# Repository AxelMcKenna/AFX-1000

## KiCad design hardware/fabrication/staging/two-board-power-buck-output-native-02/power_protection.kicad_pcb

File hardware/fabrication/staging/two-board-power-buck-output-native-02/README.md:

# Power/protection — local U23 output-capacitor bank

This checkpoint closes **eight physical connections**, bringing the power board
to **2,525 opens**. It remains **not ready for fabrication**. Open
[power_protection.kicad_pro](power_protection.kicad_pro) in KiCad.

## Placement and copper

C226–C229 retain their existing 47 µF / 25 V X7S components and footprints.
C227 moves to the front at (295,111.35) mm; C226, C228 and C229 form a back-side
bank at x=295 mm and y=111.35, 114.85 and 118.35 mm. This puts their connections
next to the inductor output, instead of beyond the regulator's feedback region.
No other component moves and no schematic pin/net assignment changes.

The front capacitor connects to L23's output with a 1 mm-wide, 5.765 mm path.
The back bank uses 1 mm-wide output and ground buses with 3.5 mm between adjacent
lands. Paired conventional 0.60/0.30 mm vias join the front and back output and
ground copper. A further pair brings the bank return to U23's PGND pin 9.
The return uses a 1 mm back-side path and a short 0.4 mm package approach.
Six vias and 17 tracks are added in 16 declared route sections.

These dimensions describe the actual construction. Effective capacitance,
loop stability, loss/temperature, switching noise and final copper-stack
capacity remain to be qualified. The output sense route and wider power/ground
planes remain unfinished. Completing this local return does not qualify the
whole power stage.

## Checks

| Item | Result |
| --- | --- |
| Electrical parts / total footprints | 1,088 / 1,103 |
| Schematic pins / mapped native pads | 3,424 / 3,485 |
| Tracks / through vias | 2,133 / 130 |
| Uncapped native opens | 2,525, down from 2,533 |
| Geometry / schematic parity / ERC errors | 0 / 0 / 0 |
| Retained isolated-reference warnings | 2 |
| Prior physical connection groups retained | All 3,271 |
| Moved footprints / changed native pads | 4 / 8 |
| Minimum drill-edge-to-SMD clearance, all vias | 0.165 mm |

The [independent audit](buck-output-audit.json) checks the saved native pad
polygons, every added track/via, the full unchanged schematic pin/net map,
unchanged earlier copper and all previous connection groups. It confirms all
four output capacitor pins connect to L23 and all four return pins connect to
U23 PGND. The eight moved pad polygons match the declared transforms within
0.000001 mm. Courtyard, board edge, mount and provisional receiving/context
checks pass; complete installed fit remains open.

The first native trial reported a copper-sliver warning. The selected successor
replaces acute and overlapping joins with shared trunks and has zero geometry
findings, with no rules suppressed. The [construction record](buck-output-routing.json)
and [native review](review.json) identify the selected source.
The [full native capture](../two-board-power-routing-inputs-2525-buck-output/capture.json)
contains 5,990 objects; its independent cluster-gap sum agrees with 2,525 opens.
The DRC output list remains capped at 499 records and is not the full open count.

## Actual copper views

| Front | Back, in top-view coordinates |
| --- | --- |
|  |  |

[Inner layers](plots/inner-contact-sheet.png) · [Local front detail](plots/local-front.png)
· [Local back detail](plots/local-back.png) · [Visual review](plots/visual-review.json)

## Remaining work

Route the output sense, configuration and enables, and complete input/ground
planes. Regroup U20/AUX and other critical circuits; route the relocated buffer's
bypass. The [source-net reconciliation](rejected-source-net-status.json) retains
eight complete and 44 incomplete formerly rejected nets. Signal main remains
at 251 opens and a missing ESS codec footprint. Remaining electrical checks,
accepted ESS package inputs, interfaces, effective capacitance, stack/BOM/process,
manufacturing outputs, cooling/supports and installed housing fit remain required.
No fabrication release or order has been made.

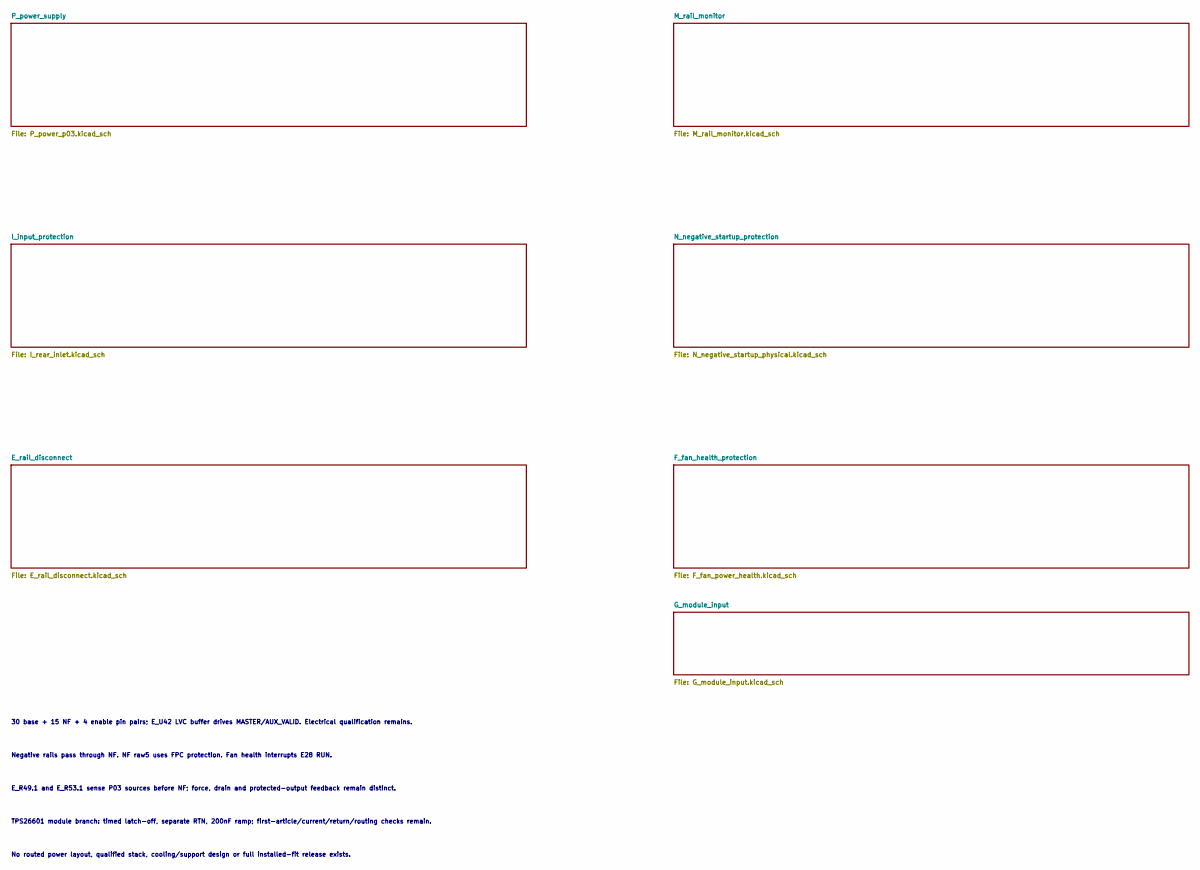
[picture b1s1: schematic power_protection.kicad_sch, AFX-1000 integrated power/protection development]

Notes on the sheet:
30 base + 15 NF + 4 enable pin pairs; E_U42 LVC buffer drives MASTER/AUX_VALID. Electrical qualification remains.
Negative rails pass through NF. NF raw5 uses FPC protection. Fan health interrupts E28 RUN.
E_R49.1 and E_R53.1 sense P03 sources before NF; force, drain and protected-output feedback remain distinct.
TPS26601 module branch: timed latch-off, separate RTN, 200nF ramp; first-article/current/return/routing checks remain.
No routed power layout, qualified stack, cooling/support design or full installed-fit release exists.

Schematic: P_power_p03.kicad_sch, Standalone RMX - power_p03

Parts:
P_C1, P_C63: 10uF 63V X7R; C_1210_3225Metric
P_C2, P_C3, P_C5, P_C6, P_C8, P_C9, P_C37, P_C42, P_C52, P_C57, P_C64, P_C65, P_C67, P_C68, P_C70, P_C204, P_C205, P_C224, P_C225, P_C254: 22uF 50V X7R 20% TDK C3225X7R1H226M250AC; C_1210_3225Metric
P_C4, P_C7, P_C10, P_C35, P_C38, P_C40, P_C43, P_C50, P_C53, P_C55, P_C58, P_C59, P_C61, P_C66, P_C69, P_C71: 100nF 50V X7R; C_0805_2012Metric
P_C11, P_C30, P_C107, P_C108: 100nF 16V X7R; C_0805_2012Metric
P_C12, P_C14, P_C73, P_C75: 68pF 50V C0G 5%; C_0805_2012Metric
P_C13, P_C15, P_C74, P_C76: 330nF 16V X7R; C_0805_2012Metric
P_C31: 2.2uF 16V X7R; C_0805_2012Metric
P_C32, P_C33: 1uF film 63V 10% MKS2C041001F00KSSD; C_Rect_L7.2mm_W5.0mm_P5.00mm
P_C34, P_C39, P_C49, P_C54, P_C240: 47nF 50V C0G 5%; C_1210_3225Metric
P_C36, P_C41, P_C51, P_C56: 10uF 50V X7R; C_1210_3225Metric
P_C60, P_C62, P_C105: 1uF 50V X7R; C_0805_2012Metric
P_C72, P_C210, P_C211, P_C230, P_C231: 100nF 50V X7R 10% TDK C1005X7R1H104K050BB; C_0402_1005Metric
P_C101, P_C102: 2.2uF 100V X7R; C_1210_3225Metric
P_C103: 220uF 35V electrolytic 20% (EEUFR1V221); CP_Radial_D8.0mm_P3.50mm
P_C104: 1uF 50V X7R; C_1210_3225Metric
P_C106: 10uF 25V X7R 10% TDK C3225X7R1E106K250AC; C_1210_3225Metric
P_C109: 1nF 16V C0G 5%; C_0805_2012Metric
P_C110: 10nF 25V C0G 5% KEMET C0603C103J3GACTU; C_0603_1608Metric
P_C113: 1uF 100V X7S 10% TDK C2012X7S2A105K125AE; C_0805_2012Metric
P_C200, P_C220: 4.7uF 25V X7R 10% TDK C2012X7R1E475K125AB; C_0805_2012Metric
P_C201, P_C221, P_C255, P_C301, P_C302: 100nF 50V X7R; C_0603_1608Metric
P_C202, P_C203, P_C222, P_C223: 2.2uF 50V X7R 10% TDK C2012X7R1H225K125AC; C_0805_2012Metric
P_C206, P_C207, P_C208, P_C209, P_C226, P_C227, P_C228, P_C229: 47uF 25V X7S 20% TDK C3225X7S1E476M250AC; C_1210_3225Metric
P_C241: 1uF 25V X7R; C_1210_3225Metric
P_C242, P_C243, P_C244, P_C245, P_C246, P_C247, P_C248, P_C249, P_C250, P_C251: 100nF 25V C0G 5% KEMET C1206C104J3GACTU; C_1206_3216Metric
P_C252, P_C253: 1uF 16V X7R; C_1210_3225Metric
P_C300: 10nF 50V C0G 5%; C_0805_2012Metric
P_C401, P_C402: 100nF 50V X7R C0603C104K5RACTU; C0603
P_C403: 10nF 50V C0G C0603C103J5GACTU; C0603
P_D1, P_D2, P_D3, P_D4, P_D103: SS16-E3/61T; D_SMA
P_D101: SMBJ33CA-E3/52; D_SMB
P_D102: BAS116,215; SOT-23
P_J2: Header6; PinHeader_1x06_P2.54mm_Vertical
P_J3: Header2; PinHeader_1x02_P2.54mm_Vertical
P_J20, P_J21, P_J23, P_J24: Wurth 7466003R M3 SMT; Wurth_7466003R
P_J22: P03 READY test; PinHeader_1x03_P2.54mm_Vertical
P_J103: Bare POWER_READY probe pads, no fitted header; Probe2_P2.54_D1
P_J104: JST B3B-XH-A (XHP-3/SXH-001T-P0.6); JST_XH_B3B-XH-A_1x03_P2.50mm_Vertical
P_J106: JST B4B-XH-A (XHP-4/SXH-001T-P0.6); JST_XH_B4B-XH-A_1x04_P2.50mm_Vertical
P_L1, P_L6: 33uH 20% SRP7050WA-330M; SRP7050WA
P_L2, P_L3, P_L7, P_L8: 68uH 20% SRP1050WA-680M; SRP1050WA
P_L20, P_L23: 4.7uH 20% Coilcraft XAL7030-472MEC; L_Coilcraft_XAL7030-472
P_Q101: PSMN012-100YL,115; LFPAK56
P_Q102: BSS138-7-F; SOT-23
P_Q103: DMN2056U-7; SOT-23
P_R1: 300k 0.01% 5ppm; R_0805_2012Metric
P_R2, P_R3, P_R4, P_R45, P_R46: 15k 0.01% 5ppm; R_0805_2012Metric
P_R5, P_R20, P_R21, P_R34, P_R35: 330k 0.01% 5ppm; R_0805_2012Metric
P_R6, P_R7, P_R49, P_R50: 4.7k 1%; R_0805_2012Metric
P_R17, P_R19, P_R110: 1k 1%; R_0805_2012Metric
P_R18, P_R120: 100k 1%; R_0805_2012Metric
P_R22, P_R27, P_R36, P_R41, P_R243, P_R244: 100k 0.01% 5ppm; R_0805_2012Metric
P_R23, P_R28, P_R37, P_R42, P_R241: 6.8k 1%; R_0805_2012Metric
P_R24, P_R38: 9.09k 1%; R_0805_2012Metric
P_R25, P_R39, P_R47, P_R306: 200k 0.01% 5ppm; R_0805_2012Metric
P_R26, P_R40, P_R308: 180k 0.01% 5ppm; R_0805_2012Metric
P_R29, P_R43: 5.62k 1%; R_0805_2012Metric
P_R44: 240k 0.01% 5ppm; R_0805_2012Metric
P_R48, P_R301, P_R303, P_R305, P_R307, P_R309, P_R314: 10k 0.01% 5ppm; R_0805_2012Metric
P_R101, P_R103, P_R117: 309k 0.1% 10ppm; R_0805_2012Metric
P_R102: 40.2k 0.1% 10ppm; R_0805_2012Metric
P_R104: 28k 0.1% 10ppm; R_0805_2012Metric
P_R105: 68.1k 0.1% 10ppm; R_0805_2012Metric
P_R106, P_R109, P_R118, P_R119: 10k 0.1% 10ppm; R_0805_2012Metric
P_R107: 4.02k 0.1% 10ppm; R_0805_2012Metric
P_R108: 11.7k 0.1% 10ppm; R_0805_2012Metric
P_R111, P_R204, P_R224, P_R246: 10k 1%; R_0805_2012Metric
P_R112, P_R114: 47k 1%; R_0805_2012Metric
P_R113: 3.3k 1%; R_0805_2012Metric
P_R115: 30.9k 0.1% 10ppm; R_0805_2012Metric
P_R116: 3.09k 0.1% 10ppm; R_0805_2012Metric
P_R121: 100 1%; R_0805_2012Metric
P_R130: 49.9 0.01% 5ppm; R_0805_2012Metric
P_R200: 9k 0.01% 2ppm Susumu RG2012L-902-L-T1; R_0805_2012Metric
P_R201: 1k 0.01% 2ppm Susumu RG2012L-102-L-T1; R_0805_2012Metric
P_R202, P_R222: 24.3k 1%; R_0805_2012Metric
P_R203, P_R223: 18.2k 0.1% 25ppm Panasonic ERA6AEB1822V; R_0805_2012Metric
P_R205, P_R225: 22k 1%; R_0805_2012Metric
P_R206: 54.9 0.1% 25ppm Panasonic ERA6AEB549V; R_0805_2012Metric
P_R220: 11k 0.01% 5ppm; R_0805_2012Metric
P_R221, P_R311: 1k 0.01% 5ppm; R_0805_2012Metric
P_R240: 100 0.01% 5ppm; R_0805_2012Metric
P_R242: 120 0.01% 5ppm; R_0805_2012Metric
P_R245: 2.21k 1%; R_0805_2012Metric
P_R300, P_R302: 87.6k 0.01% 5ppm; R_0805_2012Metric
P_R304: 324k 0.01% 5ppm; R_0805_2012Metric
P_R310: 590 0.01% 5ppm; R_0805_2012Metric
P_R312: 7.5k 0.01% 5ppm; R_0805_2012Metric
P_R313: 1M 0.01% 5ppm; R_0805_2012Metric
P_R315: 750k 0.01% 5ppm; R_0805_2012Metric
P_R316: 2.2k 0.1% 25ppm Panasonic ERA6AEB222V; R_0805_2012Metric
P_R401: 100k ohm TNPW0805100KBEEA; R0805
P_R402: 10M 1% CRCW080510M0FKEA; R0805
P_R403: 1k 1% CRCW12061K00FKEA; R1206
P_U1, P_U13: LT3471EDD#PBF; DFN-10-1EP_3x3mm_P0.5mm_EP1.65x2.38mm
P_U4: REF5025EIDR; SOIC-8_3.9x4.9mm_P1.27mm
P_U5: OPA4192ID; SOIC-14_3.9x8.7mm_P1.27mm
P_U6, P_U24: OPA2192ID; SOIC-8_3.9x4.9mm_P1.27mm
P_U7: LT3080IMS8E#PBF; MSOP-8-1EP_3x3mm_P0.65mm_EP1.68x1.88mm
P_U8: LT3080IQ#PBF; TO-263-5_TabPin3
P_U10, P_U11: LT3090IDD#PBF; DFN-10-1EP_3x3mm_P0.5mm_EP1.65x2.38mm
P_U12: LT1634AIS8-2.5#PBF; SOIC-8_3.9x4.9mm_P1.27mm
P_U20, P_U23: TPS543620RPYR; TPS543620_RPY0014A
P_U21: ADR4550BRZ; SOIC-8_3.9x4.9mm_P1.27mm
P_U22: LT3045IDD#PBF; DFN-10-1EP_3x3mm_P0.5mm_EP1.65x2.38mm
P_U25: LTC2910HGN#PBF; SSOP-16_3.9x4.9mm_P0.635mm
P_U26: SN74LVC1G97DBVR; SOT-23-6
P_U101: TPS26630RGER; Texas_RGE0024H_VQFN-24-1EP_4x4mm_P0.5mm_EP2.7x2.7mm
P_U102: TPS7A1601DGNR; MSOP-8-1EP_3x3mm_P0.65mm_EP1.68x1.88mm
P_U103: TLV7011DBVR; SOT-23-5
P_U201: TPS389001DSET; TI_DSE0006A
P_U202: SN74AUP1G17DCKR; TI_DCK0005A

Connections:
/P_power_supply/AUX_FB: P_R109.1, P_R130.2, P_U102.2 (FB)
/P_power_supply/AUX_START_DELAY: P_C110.1 (+), P_U102.7 (DELAY)
/P_power_supply/AX03_RUN_DRIVE: P_R403.1, P_U202.4 (Y)
/P_power_supply/AX03_SOURCE_CT: P_C403.1, P_U201.5 (CT)
/P_power_supply/AX03_SOURCE_RESET: P_R401.2, P_R402.1, P_U201.6 (RESET_N), P_U202.2 (A)
/P_power_supply/BLOCK_DRV: P_Q102.1 (GATE), P_U101.4 (DRV)
/P_power_supply/BLOCK_GATE: P_Q101.4 (GATE), P_Q102.3 (DRAIN), P_U101.3 (B_GATE)
/P_power_supply/CUK_NODE: P_C1.2, P_D2.2 (A), P_L3.1
/P_power_supply/FAST_OV_GATE: P_Q103.1 (GATE), P_R120.1, P_R121.2
/P_power_supply/FAST_OV_OUT: P_R117.1, P_R121.1, P_U103.1 (OUT)
/P_power_supply/FAST_OV_REF: P_C109.1 (+), P_R118.2, P_R119.1, P_U103.4 (IN-)
/P_power_supply/FAST_OV_SENSE: P_R115.2, P_R116.1, P_R117.2, P_U103.3 (IN+)
/P_power_supply/INPUT_ILIM: P_R107.1, P_U101.10 (ILIM)
/P_power_supply/INPUT_OV: P_D102.1 (ANODE), P_R103.2, P_R104.1, P_U101.7 (OVP)
/P_power_supply/INPUT_PGTH: P_R105.2, P_R106.1, P_U101.15 (PGTH)
/P_power_supply/INPUT_SLEW: P_C105.1 (+), P_U101.9 (dVdT)
/P_power_supply/INPUT_UV: P_R101.2, P_R102.1, P_U101.6 (UVLO)
/P_power_supply/LO_CUK_NODE: P_C63.2, P_D4.2 (A), P_L8.1
/P_power_supply/LO_N_FB: P_C75.2, P_R46.2, P_R47.1, P_U13.4 (FB2P)
/P_power_supply/LO_N_RMID: P_R47.2, P_R48.1
/P_power_supply/LO_N_SS: P_C76.1, P_R50.2, P_U13.7 (SHDN_SS2)
/P_power_supply/LO_N_SW: P_C63.1, P_L7.2, P_U13.6 (SW2)
/P_power_supply/LO_P_FB: P_C73.2, P_R44.2, P_R45.1, P_U13.1 (FB1N)
/P_power_supply/LO_P_SS: P_C74.1, P_R49.2, P_U13.9 (SHDN_SS1)
/P_power_supply/LO_P_SW: P_D3.2 (A), P_L6.2, P_U13.10 (SW1)
/P_power_supply/LO_REF_1V: P_C72.1, P_R46.1, P_U13.2 (FB1P), P_U13.3 (VREF)
/P_power_supply/N12_DRIVE: P_C54.1, P_R42.1, P_U6.7 (OUT)
/P_power_supply/N12_FB: P_C54.2, P_R40.2, P_R41.1, P_U6.6 (-)
/P_power_supply/N12_RMID: P_R39.2, P_R40.1
/P_power_supply/N12_SET: P_C55.1, P_R39.1, P_R42.2, P_U11.4 (SET)
/P_power_supply/N19_DRIVE: P_C49.1, P_R37.1, P_U6.1 (OUT)
/P_power_supply/N19_FB: P_C49.2, P_R35.2, P_R36.1, P_U6.2 (-)
/P_power_supply/N19_RMID: P_R34.2, P_R35.1
/P_power_supply/N19_SET: P_C50.1, P_R34.1, P_R37.2, P_U10.4 (SET)
/P_power_supply/NREF_2V5: P_R18.1, P_R19.1, P_U12.4 (GND/ANODE), P_U12.5 (TEST)
/P_power_supply/NREF_FILTER: P_C33.1, P_R19.2, P_U6.3 (+), P_U6.5 (+)
/P_power_supply/P03_ANA_DIV: P_R242.2, P_R243.1, P_R244.1
/P_power_supply/P03_ANA_DRIVE: P_C240.1 (+), P_R241.1, P_U24.1 (OUT_A)
/P_power_supply/P03_ANA_FB: P_C240.2 (-), P_R244.2, P_U24.2 (IN_A_N)
/P_power_supply/P03_ANA_SET: P_C241.1 (+), P_R241.2, P_R242.1, P_U22.7 (SET)
/P_power_supply/P03_AUX_TRIM: P_R108.2, P_R130.1
/P_power_supply/P03_A_BOOT: P_C221.1 (+), P_U23.14 (BOOT)
/P_power_supply/P03_A_BP5: P_C220.1 (+), P_U23.6 (BP5)
/P_power_supply/P03_A_ENABLE: P_R224.2, P_R225.1, P_U23.7 (EN)
/P_power_supply/P03_A_FB: P_R220.2, P_R221.1, P_U23.4 (FB)
/P_power_supply/P03_A_FSEL: P_R222.1, P_U23.1 (SYNC_FSEL)
/P_power_supply/P03_A_MODE: P_R223.1, P_U23.2 (MODE)
/P_power_supply/P03_D_BOOT: P_C201.1 (+), P_U20.14 (BOOT)
/P_power_supply/P03_D_BP5: P_C200.1 (+), P_U20.6 (BP5)
/P_power_supply/P03_D_ENABLE: P_R204.2, P_R205.1, P_U20.7 (EN)
/P_power_supply/P03_D_FB: P_R201.1, P_R206.2, P_U20.4 (FB)
/P_power_supply/P03_D_FB_TRIM: P_R200.2, P_R206.1
/P_power_supply/P03_D_FSEL: P_R202.1, P_U20.1 (SYNC_FSEL)
/P_power_supply/P03_D_MODE: P_R203.1, P_U20.2 (MODE)
/P_power_supply/P03_MON_ANA: P_R302.2, P_R303.1, P_U25.2 (V2)
/P_power_supply/P03_MON_BUCK_OK: P_U25.5 (V5), P_U26.4 (Y)
/P_power_supply/P03_MON_DIG: P_R300.2, P_R301.1, P_U25.1 (V1)
/P_power_supply/P03_MON_N12: P_R314.2, P_R315.1, P_U25.8 (V8)
/P_power_supply/P03_MON_N19: P_R312.2, P_R313.1, P_U25.7 (V7)
/P_power_supply/P03_MON_NEG_BIAS: P_R310.2, P_R311.1, P_R312.1, P_R314.1
/P_power_supply/P03_MON_P12: P_R306.2, P_R307.1, P_U25.4 (V4)
/P_power_supply/P03_MON_P19: P_R304.2, P_R305.1, P_U25.3 (V3)
/P_power_supply/P03_MON_REF: P_R310.1, P_U25.10 (REF)
/P_power_supply/P03_MON_TIMER: P_C300.1 (+), P_U25.15 (TMR)
/P_power_supply/P03_MON_VIN: P_R308.2, P_R309.1, P_U25.6 (V6)
/P_power_supply/P03_PRE6V: P_C226.1 (+), P_C227.1 (+), P_C228.1 (+), P_C229.1 (+), P_C253.1 (+), P_L23.2 (OUT), P_R220.1, P_U21.2 (VIN), P_U22.1 (IN), P_U22.2 (IN), P_U22.3 (EN_UV), P_U22.6 (PGFB)
/P_power_supply/P03_REF5: P_C252.1 (+), P_R240.1, P_U21.6 (VOUT)
/P_power_supply/P03_REF_FILTER: P_C242.1 (+), P_C243.1 (+), P_C244.1 (+), P_C245.1 (+), P_C246.1 (+), P_C247.1 (+), P_C248.1 (+), P_C249.1 (+), P_C250.1 (+), P_C251.1 (+), P_R240.2, P_U24.3 (IN_A_P)
/P_power_supply/P03_SOURCES_READY: P_R246.2, P_U20.3 (PGOOD), P_U23.3 (PGOOD), P_U26.3 (In0)
/P_power_supply/P03_SPARE_24: P_U24.6 (IN_B_N), P_U24.7 (OUT_B)
/P_power_supply/P03_SPARE_C: P_U5.8 (OUT), P_U5.9 (-)
/P_power_supply/P12_DRIVE: P_C39.1, P_R28.1, P_U5.7 (OUT)
/P_power_supply/P12_FB: P_C39.2, P_R26.2, P_R27.1, P_U5.6 (-)
/P_power_supply/P12_RMID: P_R25.2, P_R26.1
/P_power_supply/P12_SET: P_C40.1, P_R25.1, P_R28.2, P_U8.2 (SET)
/P_power_supply/P19_DRIVE: P_C34.1, P_R23.1, P_U5.1 (OUT)
/P_power_supply/P19_FB: P_C34.2, P_R21.2, P_R22.1, P_U5.2 (-)
/P_power_supply/P19_RMID: P_R20.2, P_R21.1
/P_power_supply/P19_SET: P_C35.1, P_R20.1, P_R23.2, P_U7.4 (SET)
/P_power_supply/POWER_READY: P_J22.3 (POWER_READY), P_J103.2 (POWER_READY), P_R110.2, P_R204.1, P_R224.1, P_U26.6 (In2), P_U101.16 (PGOOD)
/P_power_supply/PREF_2V5: P_C31.1, P_R17.1, P_U4.6 (VOUT)
/P_power_supply/PREF_FILTER: P_C32.1, P_R17.2, P_U5.3 (+), P_U5.5 (+)
/P_power_supply/RAW_N17: P_C56.1, P_C67.1, P_C68.1, P_C69.1, P_C75.1, P_L8.2, P_R48.2, P_U11.8 (ILIM), P_U11.9 (IN), P_U11.10 (IN), P_U11.11 (EP/IN)
/P_power_supply/RAW_N22: P_C8.1, P_C9.1, P_C10.1, P_C14.1, P_C51.1, P_C61.1, P_C62.1, P_L3.2, P_R5.2, P_R18.2, P_U6.4 (V-), P_U10.8 (ILIM), P_U10.9 (IN), P_U10.10 (IN), P_U10.11 (EP/IN)
/P_power_supply/RAW_N_FB: P_C14.2, P_R4.2, P_R5.1, P_U1.4 (FB2P)
/P_power_supply/RAW_N_SS: P_C15.1, P_R7.2, P_U1.7 (SHDN_SS2)
/P_power_supply/RAW_N_SW: P_C1.1, P_L2.2, P_U1.6 (SW2)
/P_power_supply/RAW_P17: P_C41.1, P_C64.1, P_C65.1, P_C66.1, P_C73.1, P_D3.1 (K), P_R44.1, P_U8.4 (VCONTROL), P_U8.5 (IN)
/P_power_supply/RAW_P22: P_C5.1, P_C6.1, P_C7.1, P_C12.1, P_C36.1, P_C59.1, P_C60.1, P_D1.1 (K), P_R1.1, P_U5.4 (V+), P_U7.5 (VCONTROL), P_U7.7 (IN), P_U7.8 (IN)
/P_power_supply/RAW_P_FB: P_C12.2, P_R2.2, P_R3.1, P_U1.1 (FB1N)
/P_power_supply/RAW_P_RMID: P_R1.2, P_R2.1
/P_power_supply/RAW_P_SS: P_C13.1, P_R6.2, P_U1.9 (SHDN_SS1)
/P_power_supply/RAW_P_SW: P_D1.2 (A), P_L1.2, P_U1.10 (SW1)
/P_power_supply/SPARE_OUT: P_U5.13 (SPARE-), P_U5.14 (SPARE_OUT)
/P_power_supply/SW_REF_1V: P_C11.1, P_R4.1, P_U1.2 (FB1P), P_U1.3 (VREF)
/P_power_supply/VIN_IC: P_C102.1 (+), P_C113.1 (+), P_Q101.5 (DRAIN/MB), P_R115.1, P_U101.1 (IN), P_U101.2 (IN), P_U102.5 (EN), P_U102.8 (IN)
PWR_5V_DIG_SRC: P_C30.1, P_C206.1 (+), P_C207.1 (+), P_C208.1 (+), P_C209.1 (+), P_J3.1 (5V_DIG), P_J23.1, P_L20.2 (OUT), P_R6.1, P_R7.1, P_R49.1, P_R50.1, P_R200.1, P_R300.1, P_U4.1 (EN), P_U4.2 (VIN), P_U10.5 (SHDN), P_U11.5 (SHDN); also elsewhere on the board
PWR_AGND: P_C2.2, P_C3.2, P_C4.2, P_C5.2, P_C6.2, P_C7.2, P_C8.2, P_C9.2, P_C10.2, P_C11.2, P_C13.2, P_C15.2, P_C30.2, P_C31.2, P_C32.2, P_C33.2, P_C35.2, P_C36.2, P_C37.2, P_C38.2, P_C40.2, P_C41.2, P_C42.2, P_C43.2, P_C50.2, P_C51.2, P_C52.2, P_C53.2, P_C55.2, P_C56.2, P_C57.2, P_C58.2, P_C59.2, P_C60.2, P_C61.2, P_C62.2, P_C64.2, P_C65.2, P_C66.2, P_C67.2, P_C68.2, P_C69.2, P_C70.2, P_C71.2, P_C72.2, P_C74.2, P_C76.2, P_C101.2 (-), P_C102.2 (-), P_C103.2 (-), P_C104.2 (-), P_C105.2 (-), P_C106.2 (-), P_C107.2 (-), P_C108.2 (-), P_C109.2 (-), P_C110.2 (-), P_C113.2 (-), P_C200.2 (-), P_C202.2 (-), P_C203.2 (-), P_C204.2 (-), P_C205.2 (-), P_C206.2 (-), P_C207.2 (-), P_C208.2 (-), P_C209.2 (-), P_C210.2 (-), P_C211.2 (-), P_C220.2 (-), P_C222.2 (-), P_C223.2 (-), P_C224.2 (-), P_C225.2 (-), P_C226.2 (-), P_C227.2 (-), P_C228.2 (-), P_C229.2 (-), P_C230.2 (-), P_C231.2 (-), P_C241.2 (-), P_C242.2 (-), P_C243.2 (-), P_C244.2 (-), P_C245.2 (-), P_C246.2 (-), P_C247.2 (-), P_C248.2 (-), P_C249.2 (-), P_C250.2 (-), P_C251.2 (-), P_C252.2 (-), P_C253.2 (-), P_C254.2 (-), P_C255.2 (-), P_C300.2 (-), P_C301.2 (-), P_C302.2 (-), P_C401.2, P_C402.2, P_C403.2, P_D2.1 (K), P_D4.1 (K), P_D101.2, P_D103.2 (ANODE), P_J2.2 (AGND), P_J3.2 (AGND), P_J20.1, P_J21.1, P_J22.2 (AGND), P_J103.1 (AGND), P_J104.3 (AGND), P_J106.2 (AGND), P_Q103.2 (SOURCE), P_R3.2, P_R22.2, P_R24.2, P_R27.2, P_R29.2, P_R36.2, P_R38.2, P_R41.2, P_R43.2, P_R45.2, P_R102.2, P_R104.2, P_R106.2, P_R107.2, P_R109.2, P_R111.2, P_R112.2, P_R114.2, P_R116.2, P_R119.2, P_R120.2, P_R201.2, P_R202.2, P_R203.2, P_R205.2, P_R221.2, P_R222.2, P_R223.2, P_R225.2, P_R243.2, P_R245.2, P_R301.2, P_R303.2, P_R305.2, P_R307.2, P_R309.2, P_R311.2, P_R402.2, P_U1.5 (FB2N), P_U1.11 (GND_EP), P_U4.4 (GND), P_U5.10 (+), P_U5.11 (V-), P_U5.12 (SPARE+), P_U6.8 (V+), P_U10.3 (GND), P_U11.3 (GND), P_U12.6 (VOUT/CATHODE), P_U13.5 (FB2N), P_U13.11 (GND_EP), P_U20.5 (AGND), P_U20.9 (PGND), P_U20.11 (PGND), P_U21.4 (GND), P_U22.5 (ILIM), P_U22.8 (GND), P_U22.11 (EP_GND), P_U23.5 (AGND), P_U23.9 (PGND), P_U23.11 (PGND), P_U24.4 (V_N), P_U24.5 (IN_B_P), P_U25.9 (GND), P_U25.13 (DIS), P_U25.14 (SEL), P_U26.1 (In1_AND_CONFIG_LOW), P_U26.2 (GND), P_U101.8 (GND), P_U101.25 (EP/GND), P_U102.4 (GND), P_U102.9 (EP/GND), P_U103.2 (VEE), P_U201.2 (GND), P_U202.3 (GND); also elsewhere on the board
PWR_DC_IN: P_C101.1 (+), P_D101.1, P_Q101.1 (SOURCE), P_Q101.2 (SOURCE), P_Q101.3 (SOURCE), P_Q102.2 (SOURCE), P_R101.1, P_R103.1, P_U101.5 (IN_SYS); also elsewhere on the board
PWR_MODULE_FEED_IN: P_C2.1, P_C3.1, P_C4.1, P_C70.1, P_C71.1, P_C103.1 (+), P_C104.1 (+), P_C202.1 (+), P_C203.1 (+), P_C204.1 (+), P_C205.1 (+), P_C210.1 (+), P_C211.1 (+), P_C222.1 (+), P_C223.1 (+), P_C224.1 (+), P_C225.1 (+), P_C230.1 (+), P_C231.1 (+), P_C255.1 (+), P_D103.1 (CATHODE), P_L1.1, P_L2.1, P_L6.1, P_L7.1, P_R105.1, P_R114.1, P_R308.1, P_U1.8 (VIN), P_U13.8 (VIN), P_U20.8 (VIN), P_U20.12 (VIN), P_U23.8 (VIN), P_U23.12 (VIN), P_U24.8 (V_P), P_U101.17 (OUT), P_U101.18 (OUT); also elsewhere on the board
PWR_N12_SOURCE: P_C57.1, P_C58.1, P_J2.5 (N12), P_R43.1, P_R315.2, P_U11.1 (OUT), P_U11.2 (OUT); also elsewhere on the board
PWR_N19_SOURCE: P_C52.1, P_C53.1, P_J2.3 (N19), P_R38.1, P_R313.2, P_U10.1 (OUT), P_U10.2 (OUT); also elsewhere on the board
PWR_P03_SOURCES_READY: P_J22.1 (ALL_SOURCES_READY), P_J106.4 (SOURCE_READY), P_R316.2, P_U25.12 (RST_ACTIVE_LOW); also elsewhere on the board
PWR_P12_SRC: P_C42.1, P_C43.1, P_J2.4 (P12), P_R29.1, P_R306.1, P_U8.3 (OUT/TAB); also elsewhere on the board
PWR_P19_SRC: P_C37.1, P_C38.1, P_J2.1 (P19), P_R24.1, P_R304.1, P_U7.1 (OUT), P_U7.2 (OUT), P_U7.3 (OUT), P_U7.9 (EP/OUT); also elsewhere on the board
PWR_POWER_RUN: P_J104.2 (POWER_RUN), P_Q103.3 (DRAIN), P_R112.1, P_U101.12 (SHDN), P_U102.3 (PG), P_U201.1 (SENSE); also elsewhere on the board
PWR_RUN_BEFORE_FAN: P_J106.3 (POWER_RUN), P_R403.2; also elsewhere on the board
PWR_SWITCH_SUPPLY: P_J104.1 (SWITCH_SUPPLY), P_R113.2; also elsewhere on the board
PWR_V2V5_AUX: P_C106.1 (+), P_C107.1 (+), P_C108.1 (+), P_C301.1 (+), P_C302.1 (+), P_C401.1, P_C402.1, P_D102.3 (CATHODE), P_J106.1 (V2V5_AUX), P_R108.1, P_R110.1, P_R111.1, P_R113.1, P_R118.1, P_R246.1, P_R316.1, P_R401.1, P_U25.16 (VCC), P_U26.5 (VCC), P_U102.1 (OUT), P_U103.5 (VCC), P_U201.3 (MR), P_U201.4 (VDD), P_U202.5 (VCC); also elsewhere on the board
PWR_V5_REG_SRC: P_C254.1 (+), P_J2.6 (V5_REG), P_J24.1, P_R245.1, P_R302.1, P_U22.9 (OUTS), P_U22.10 (OUT); also elsewhere on the board

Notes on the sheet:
AX03 prototype: only J106.3 buffered; internal POWER_RUN, R113 and PG topology retained. No physical/fabrication release.

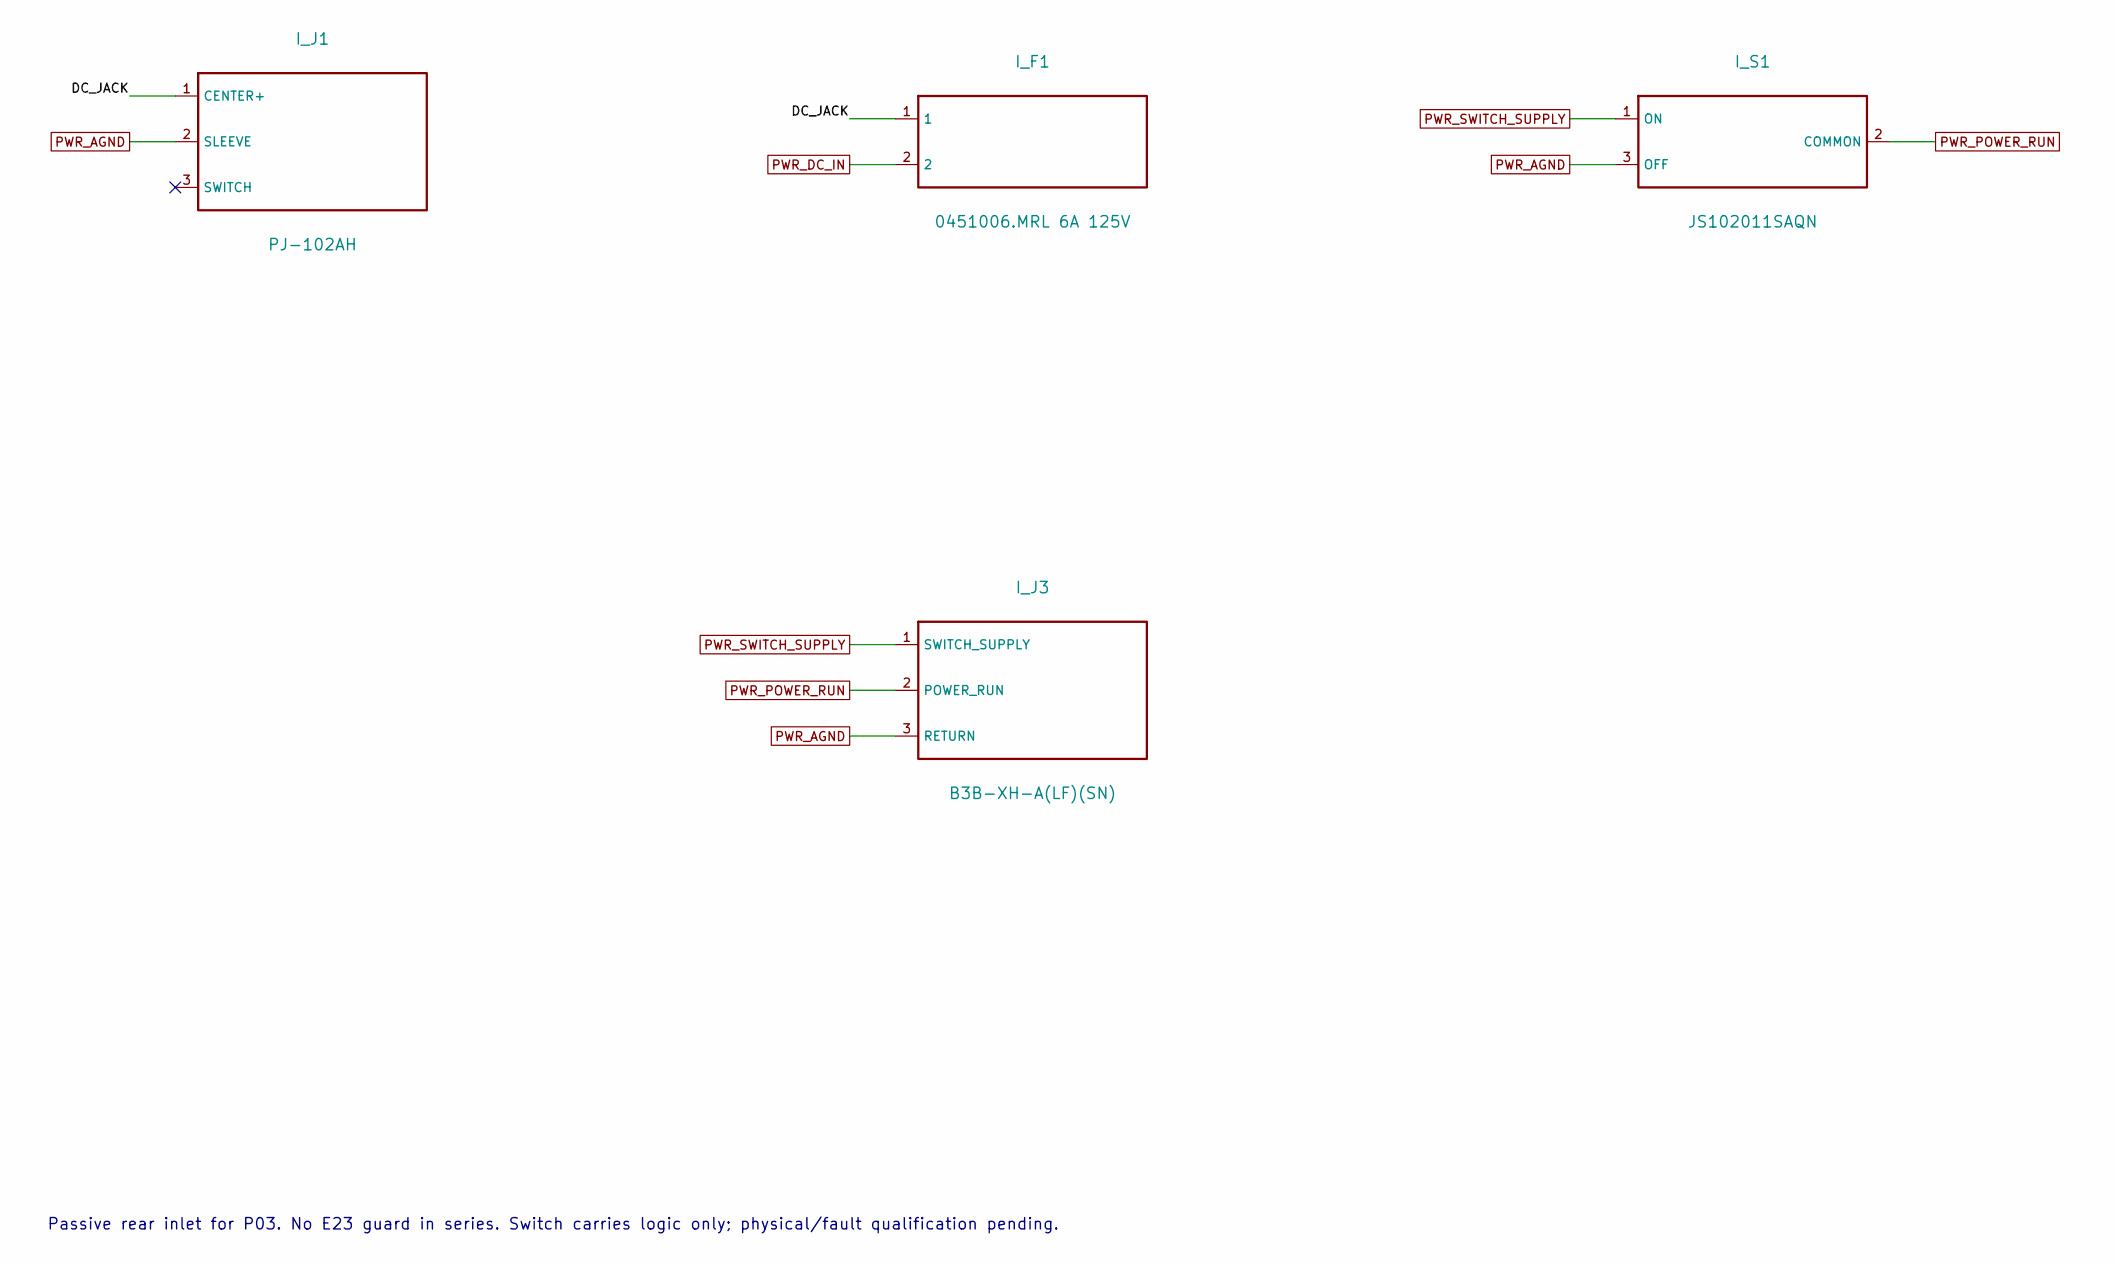
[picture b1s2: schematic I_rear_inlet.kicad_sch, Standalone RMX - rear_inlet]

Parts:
I_F1: 0451006.MRL 6A 125V; Fuse_Littelfuse-NANO2-451_453
I_J1: PJ-102AH; PJ102AH_RearEdge_E23
I_J3: B3B-XH-A(LF)(SN); JST_XH_B3B-XH-A_1x03_P2.50mm_Vertical
I_S1: JS102011SAQN; JS102011SAQN_RearEdge_E23

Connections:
/I_input_protection/DC_JACK: I_F1.1, I_J1.1 (CENTER+)
PWR_AGND: I_J1.2 (SLEEVE), I_J3.3 (RETURN), I_S1.3 (OFF); also elsewhere on the board
PWR_DC_IN: I_F1.2; also elsewhere on the board
PWR_POWER_RUN: I_J3.2 (POWER_RUN), I_S1.2 (COMMON); also elsewhere on the board
PWR_SWITCH_SUPPLY: I_J3.1 (SWITCH_SUPPLY), I_S1.1 (ON); also elsewhere on the board

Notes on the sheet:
Passive rear inlet for P03. No E23 guard in series. Switch carries logic only; physical/fault qualification pending.
